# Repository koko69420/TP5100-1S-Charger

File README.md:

# TP5100 1S Li-Ion Battery Charger (V1 — KiCad Learning Design)

A dedicated switch-mode lithium-ion battery charging board based on the **TP5100** synchronous step-down charging management IC, designed in KiCad with full production Gerbers and documentation.

> [!NOTE]
> **Project Context (V1 Learning Design)**  
> This board was designed in November 2025 as one of the author's very first PCB designs to learn KiCad—mastering schematic capture, custom footprint creation, and PCB trace routing.  
> 
> A subsequent ultra-compact redesign is available: [**TP5100 Micro Charging Module (V2)**](https://github.com/koko69420/TP5100-Charging-Module), which achieves a **66% footprint reduction** (down to 20.0 mm × 16.5 mm) with 1S/2S selectable charging.

---

## 3D Renders & Schematic

### 3D Photorealistic Views

| Top View | Bottom View |
| :---: | :---: |
|  |  |

### Electrical Schematic

---

## Evolution & Version Comparison

| Parameter | V1: KiCad Learning Board (This Repo) | [V2: Micro Module Redesign](https://github.com/koko69420/TP5100-Charging-Module) |
| :--- | :--- | :--- |
| **Role & Context** | Initial design created to learn KiCad | Ultra-compact miniaturized redesign |
| **Board Dimensions** | **55.5 mm × 17.6 mm** (977 mm²) | **20.0 mm × 16.5 mm** (330 mm²) — *66% smaller* |
| **Edge Geometry** | Standard rectangular (90° corners) | Chamfered / rounded corner arcs |
| **Battery Topology** | 1S dedicated (4.2V) | 1S (4.2V) / 2S (8.4V) solder-jumper selectable |
| **Max Charge Current** | Up to 2.0 A | Up to 2.0 A |
| **Input Supply** | 5.0 V – 18.0 V DC | 5.0 V – 18.0 V DC |
| **Component Density** | Spacious layout for easy hand-assembly | High-density double-sided SMD placement |
| **Thermal Strategy** | Distributed copper pours | Thermal relief via stitching under IC |

---

## Features

- **High-Efficiency Switch-Mode Charging**:
  - Utilizes the TP5100 buck switching management IC operating at high frequency (up to 2A charge current).
  - Superior thermal performance and energy efficiency compared to linear chargers (such as the TP4056).
- **1S Lithium-Ion Cell Profile**:
  - Configured for single-cell 4.2V float voltage charging.
  - Multi-stage Constant Current (CC) / Constant Voltage (CV) charging with trickle pre-charging for over-discharged cells.
- **Protection & Monitoring**:
  - Dual LED charging status indicators (Charging / Standby & Complete).
  - Input over-voltage and thermal shutdown protection.
- **Manufacturing-Ready Production Files**:
  - Pre-generated RS-274X Gerber layers and Excellon NC drill files ready for standard PCB fabrication.

---

## Hardware Specification

| Parameter | Value | Unit |
| :--- | :--- | :--- |
| **Charger Controller** | TP5100 | — |
| **Input Voltage Range** | 5.0 – 18.0 | V DC |
| **Battery Configuration** | 1S (1 Cell) | — |
| **Float Voltage** | 4.2 | V |
| **Charge Current** | Configurable up to 2.0 | A |
| **Architecture** | Synchronous Buck Switching | — |
| **PCB Form Factor** | 55.5 mm × 17.6 mm (2-Layer FR4, 1.6 mm thickness, 1 oz copper) | — |

---

## Project Structure

```text
TP5100-1S-Charger/
├── Schematic.pdf                     # Complete electrical schematic
├── front.png                         # 3D PCB front render
├── back.png                          # 3D PCB back render
├── why.txt                           # Project inception note ("Learning KiCad")
├── TP5100_1S_Charger.kicad_sch       # KiCad schematic design
├── TP5100_1S_Charger.kicad_pcb       # KiCad PCB board layout
├── TP5100_1S_Charger.kicad_pro       # KiCad project file
├── TP5100_1S_Charger-F_Cu.gbr        # Top copper layer
├── TP5100_1S_Charger-B_Cu.gbr        # Bottom copper layer
├── TP5100_1S_Charger-F_Mask.gbr      # Top solder mask
├── TP5100_1S_Charger-B_Mask.gbr      # Bottom solder mask
├── TP5100_1S_Charger-F_Silkscreen.gbr# Top silkscreen
├── TP5100_1S_Charger-B_Silkscreen.gbr# Bottom silkscreen
├── TP5100_1S_Charger-Edge_Cuts.gbr   # Board contour outline
├── TP5100_1S_Charger-PTH.drl         # Plated through-hole drill file
├── TP5100_1S_Charger-NPTH.drl        # Non-plated through-hole drill file
├── .gitignore                        # Git ignore rules
└── README.md                         # Project documentation
```

---

## License

Open hardware design. All rights reserved by Kausthubh Viswanath.

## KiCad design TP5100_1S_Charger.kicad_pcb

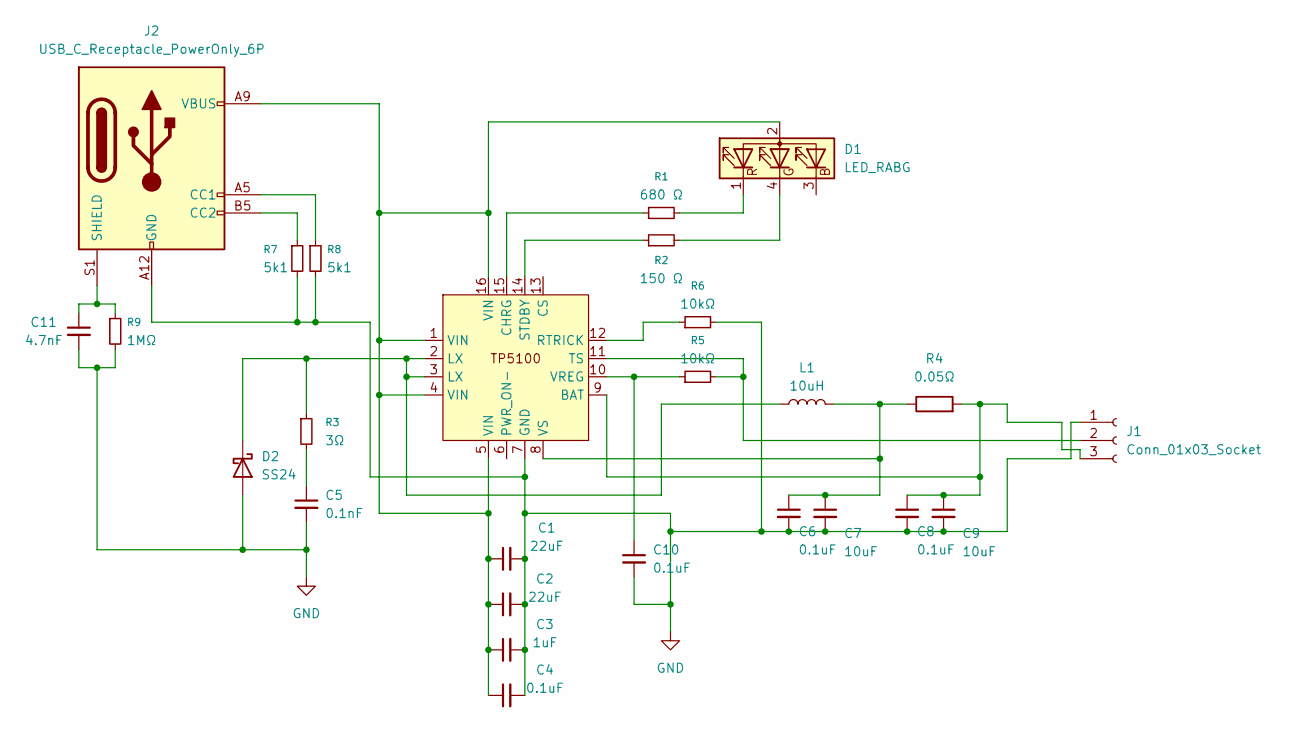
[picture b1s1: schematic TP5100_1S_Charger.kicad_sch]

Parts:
C1, C2: 22uF; C_0805_2012Metric
C3: 1uF; C_0402_1005Metric
C4: 0.1uF; C_0402_1005Metric
C5: 0.1nF; C_0603_1608Metric
C6, C8, C10: 0.1uF; C_0603_1608Metric
C7, C9: 10uF; C_1206_3216Metric
C11: 4.7nF; C_0603_1608Metric
D1: LED_RABG; LED_Cree-PLCC4_5x5mm_CW
D2: SS24; D_SMA
J1: Conn_01x03_Socket; SolderWire-1sqmm_1x03_P5.4mm_D1.4mm_OD2.7mm_Relief
J2: USB_C_Receptacle_PowerOnly_6P; USB_C_Receptacle_GCT_USB4125-xx-x_6P_TopMnt_Horizontal
L1: 10uH; L_Wuerth_HCM-7050
R1: 680 Ω; R_0402_1005Metric
R2: 150 Ω; R_0402_1005Metric
R3: 3Ω; R_0402_1005Metric
R4: 0.05Ω; R_2512_6332Metric
R5, R6: 10kΩ; R_0603_1608Metric
R7, R8: 5k1; R_0402_1005Metric
R9: 1MΩ; R_0603_1608Metric
U1: QFN_16_4x4_P0.65mm-TP5100

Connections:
GND: C1.2, C2.2, C3.2, C4.2, C5.2, C6.2, C7.2, C8.2, C9.2, C10.2, C11.2, D2.2 (A), J1.1, J2.A12 (GND), J2.B12 (GND), R6.2, R7.2, R8.2, R9.2, U1.7 (GND), U1.EP
unnamed: C5.1, R3.2
unnamed: C1.1, C2.1, C3.1, C4.1, D1.2 (A), J2.A9 (VBUS), J2.B9 (VBUS), U1.1 (VIN), U1.4 (VIN), U1.5 (VIN), U1.16 (VIN)
unnamed: D1.4 (GK), R2.2
unnamed: D1.1 (RK), R1.2
unnamed: D2.1 (K), L1.1, R3.1, U1.2 (LX), U1.3 (LX)
unnamed: J1.2, R5.2, U1.11 (TS)
unnamed: C8.1, C9.1, J1.3, R4.2, U1.9 (BAT)
unnamed: J2.A5 (CC1), R8.1
unnamed: J2.B5 (CC2), R7.1
unnamed: C11.1, J2.S1 (SHIELD), R9.1
unnamed: R1.1, U1.15 (CHRG)
unnamed: R6.1, U1.12 (RTRICK)
unnamed: R2.1, U1.14 (STDBY)
unnamed: C10.1, R5.1, U1.10 (VREG)
unnamed: C6.1, C7.1, L1.2, R4.1, U1.8 (VS)

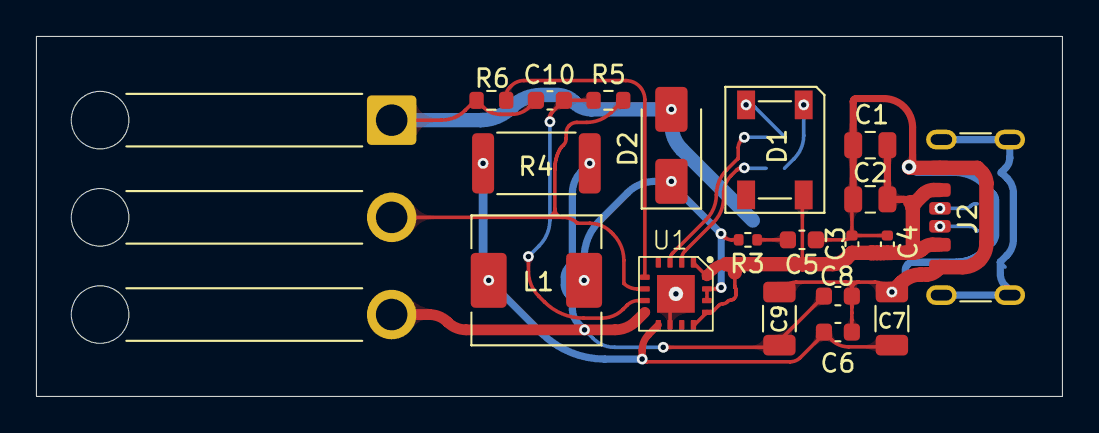
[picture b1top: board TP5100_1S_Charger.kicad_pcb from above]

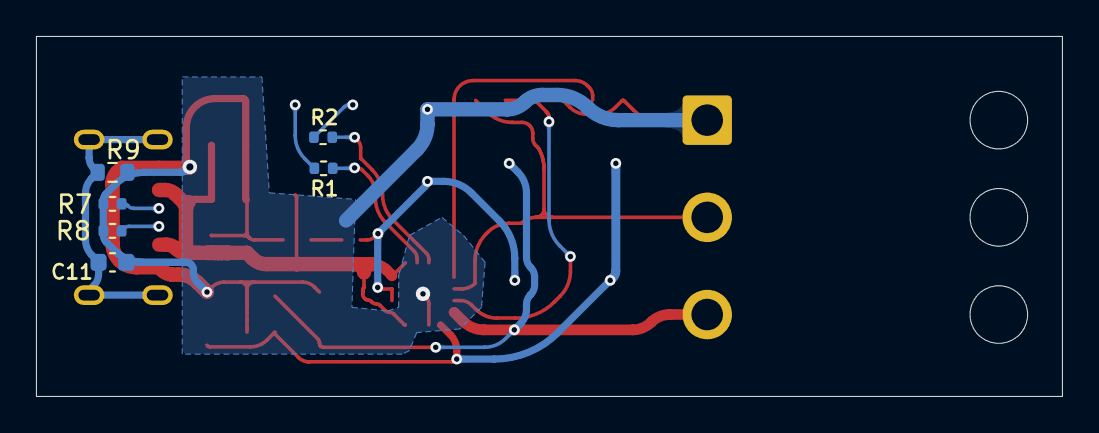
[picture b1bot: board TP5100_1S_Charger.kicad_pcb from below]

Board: 2 copper layers, 57.0 x 20.0 mm, 26 parts (6 on the bottom side), 16 nets.
